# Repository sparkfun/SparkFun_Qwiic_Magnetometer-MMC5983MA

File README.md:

# SparkFun_Qwiic_Magnetometer-MMC5983MA
========================================

[*SparkFun Qwiic Magnetometer-MMC5983MA (19921)*](https://www.sparkfun.com/products/19921)

The MMC5983MA is a highly sensitive triple axis magnetometer by MEMSIC. It is capable of sensing down to 0.4mG enabling a heading accuracy of ±0.5°. Output rates of 1000Hz, ±8G FSR, and 18-bit resolution make the MMC5983MA a phenomenal magnetic sensor for electronic compass applications.

Saturation is a problem for all mag sensors. The MMC5983MA has special built-in degaussing circuitry to clear any residual magnetization.

We've got a feature complete Arduino library supporting I<sup>2</sup>C and SPI. Just search **SparkFun MMA5983MA** in the library manager and get measuring within minutes.

Repository Contents
-------------------

* **/Documentation** - Data sheets, additional product information
* **/Firmware** - Example code 
* **/Hardware** - Eagle design files (.brd, .sch)
* **/Libraries** - Libraries for use with the <PRODUCT NAME>

Documentation
--------------
* **[Library](https://github.com/sparkfun/SparkFun_MMC5983MA_Magnetometer_Arduino_Library)** - Arduino library for the SparkFun_Qwiic_Magnetometer-MMC5983MA.
* **[Hookup Guide](https://learn.sparkfun.com/tutorials/qwiic-micro-magnetometer---mmc5983ma-hookup-guide)** - Basic hookup guide for the SparkFun Qwiic Magnetometer-MMC5983MA.

Product Versions
----------------
* [Part SKU](part URL)- Basic part and short description here
* [Retail part SKU](retail URL)- Retail packaging of standard description here
* [Any other parts this repo covers](any other URLs) - Description of said parts

License Information
-------------------

This product is _**open source**_! 

Please review the LICENSE.md file for license information. 

If you have any questions or concerns on licensing, please contact technical support on our [SparkFun forums](https://forum.sparkfun.com/viewforum.php?f=152).

Distributed as-is; no warranty is given.

- Your friends at SparkFun.

_<COLLABORATION CREDIT>_

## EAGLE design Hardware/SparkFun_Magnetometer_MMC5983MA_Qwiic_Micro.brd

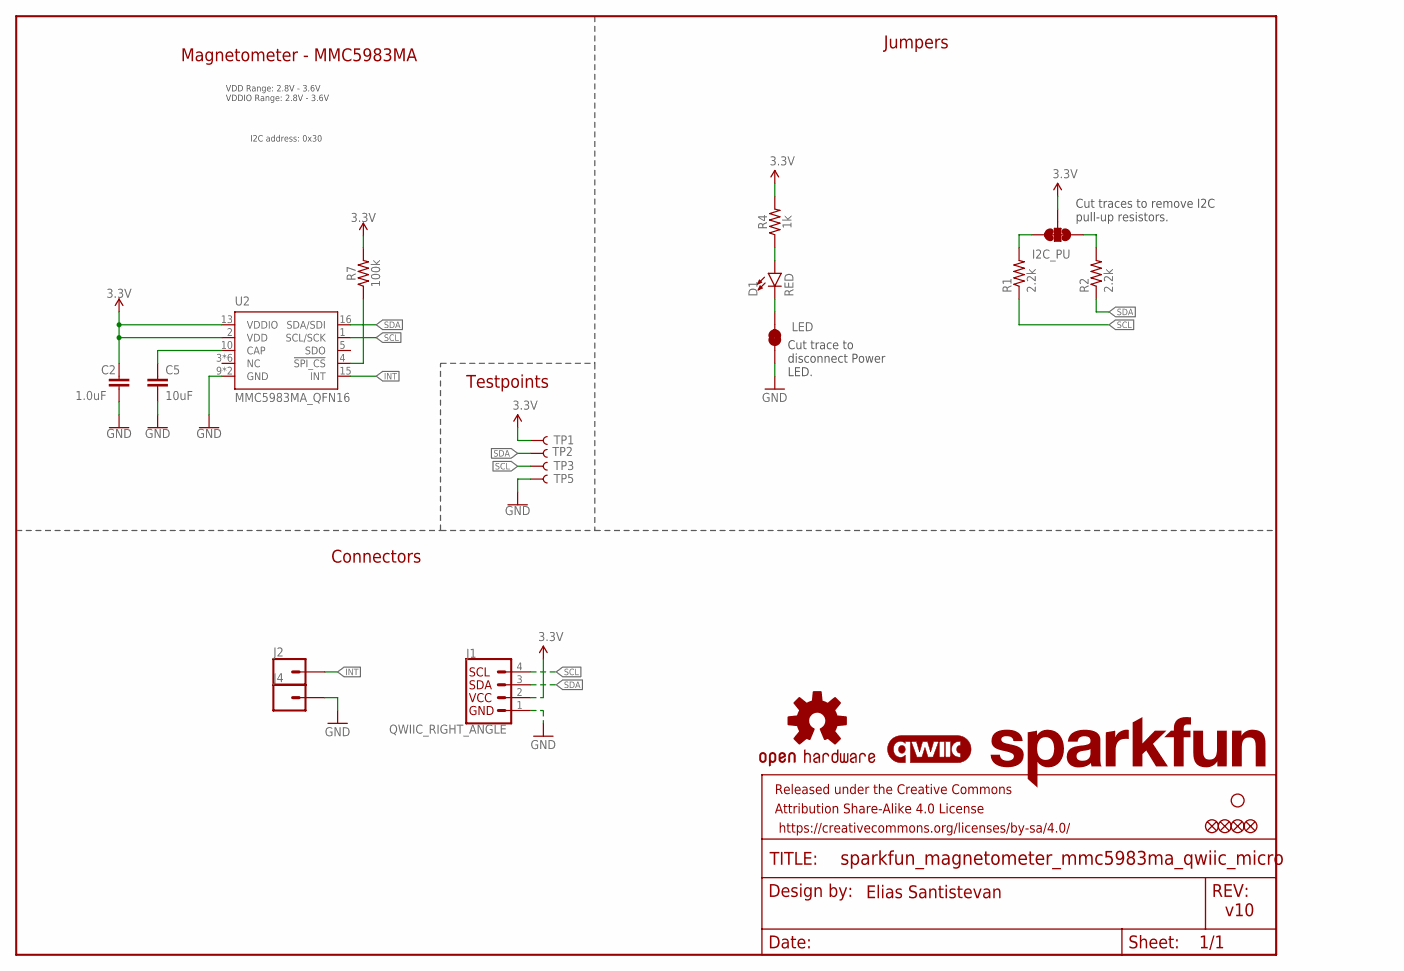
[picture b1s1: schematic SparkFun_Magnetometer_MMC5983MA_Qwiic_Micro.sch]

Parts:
C2: 1.0uF; 0402-TIGHT
C5: 10uF; 0402-TIGHT
D1: RED; LED-0402
FD1, FD2: FIDUCIALUFIDUCIAL; FIDUCIAL-MICRO
FID1, FID2: FIDUCIALUFIDUCIAL; FIDUCIAL-MICRO
FRAME1: FRAME-LETTER; CREATIVE_COMMONS
I2C_PU: S_MODE; SMT-JUMPER_3_2-NC_TRACE_SILK
J1: QWIIC_RIGHT_ANGLE; JST04_1MM_RA
J2, J4: CONN_01_1MM; 1X01_1MM_NO_SILK
LED: JUMPER-SMT_2_NC_TRACE_SILK; SMT-JUMPER_2_NC_TRACE_SILK
LOGO1: QWIIC_LOGO_4MM; QWIIC_4MM
LOGO2: OSHW-LOGOMINI; OSHW-LOGO-MINI
LOGO3: SFE_LOGO_NAMEBLANK; BLANK
R1, R2: 2.2k; 0402-TIGHT
R4: 1k; 0402-TIGHT
R7: 100k; 0402-TIGHT
STANDOFF3: STAND-OFFTIGHT; STAND-OFF-TIGHT
TP1, TP2, TP3, TP5: TEST-POINT3; PAD.03X.03
U2: MMC5983MA_QFN16; LGA-16-3X3MM-4X4PINS

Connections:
3.3V: C2.1, I2C_PU.2, J1.2, R4.2, R7.2, TP1.1, U2.2 (VDD), U2.13 (VDDIO)
!MAG_CS!: R7.1, U2.4 (!SPI_CS!)
CAP: C5.1, U2.10 (CAP)
GND: C2.2, C5.2, J1.1, J4.1, LED.1, TP5.1, U2.9 (GND), U2.11 (GND)
INT: J2.1, U2.15 (INT)
unnamed: D1.A, R4.1
unnamed: D1.C, LED.2
unnamed: I2C_PU.1, R1.2
unnamed: I2C_PU.3, R2.2
SCL: J1.4, R1.1, TP3.1, U2.1 (SCL/SCK)
SDA: J1.3, R2.1, TP2.1, U2.16 (SDA/SDI)

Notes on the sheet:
Cut traces to remove I2C pull-up resistors.
v10
Jumpers
Cut trace to disconnect Power LED.
Connectors
Elias Santistevan
Testpoints
VDD Range: 2.8V - 3.6V VDDIO Range: 2.8V - 3.6V
Magnetometer - MMC5983MA
I2C address: 0x30

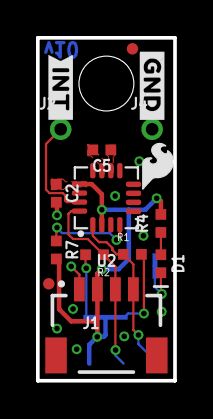
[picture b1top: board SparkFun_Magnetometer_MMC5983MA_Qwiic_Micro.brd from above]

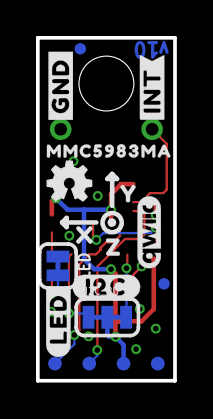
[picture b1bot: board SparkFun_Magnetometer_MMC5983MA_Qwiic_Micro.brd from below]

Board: 2 copper layers, 7.6 x 19.1 mm, 37 parts (18 on the bottom side), 11 nets.

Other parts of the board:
U$1: #INT#20
U$2: MMC5983MA331
U$3: #I2C#4
U$4, U$6: #GND#4
U$5: #INT#21
U$8: X2114
U$9: Y2115
U$10: Z2116
U$11: #LED#5
U$29: SFE_LOGO_FLAME_.1

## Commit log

2022-04-28 Places parts, fixes some schematic alignment issues
2022-04-28 Adds measures
2022-04-28 Routes the board
2022-04-29 Adds Silk, moves testpoints to grid, updates two pin connector
2022-05-02 Moves interrupt and ground pins, fixes silk, moves testpoints to 0.0375" grid
2022-05-02 Adds measures, adds 0402 RED LED from lib
2022-05-31 Increases the size of the silk, fixes measures, rolls to version v10
2022-06-02 Updates magnetometer symbol, moves I2C silk
2022-06-08 Adds Production Files

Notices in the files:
parts and their libraries:
SparkFun-Aesthetics: Licensing: Creative Commons ShareAlike 4.0 International - https://creativecommons.org/licenses/by-sa/4.0
SparkFun-Aesthetics: Released under the Creative Commons Attribution Share-Alike 4.0 License
SparkFun-Aesthetics: https://creativecommons.org/licenses/by-sa/4.0
